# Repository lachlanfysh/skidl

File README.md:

# eda-mcp

Agent-callable PCB generation engine via MCP.

AI agents send a JSON circuit specification; the engine generates KiCad
schematics and PCB layouts. Structured exceptions with machine-readable
correction candidates let the agent fix and retry without natural language.

## Architecture

See [docs/ARCHITECTURE.md](docs/ARCHITECTURE.md) for the full pipeline,
module map, correction loop mechanics, and design decisions.

## Quick Start

Requirements: Python 3.10+, KiCad 9 (for symbol/footprint libraries),
system packages for pcbnew bindings.

```bash
# Install dependencies (editable install of the SKiDL engine)
pip install -e .

# Verify the schemas and translator
pytest tests/product/test_schemas.py -v

# Run the full product test suite
pytest tests/product/ -v

# Run the telemetry tests
pytest tests/product/test_telemetry.py -v

# Run the LLM operations tests (mocked, no API key needed)
pytest tests/product/test_llm.py -v
```

### Corpus Run

The corpus runner processes a manifest of boards through the pipeline with
checkpoint/resume and bounded concurrency.

```bash
# Engine-only mode (no LLM, uses cached specs)
python3 -m corpus.run_corpus --mode engine_only --no-mcp

# With LLM translation and review (needs OPENROUTER_API_KEY)
export OPENROUTER_API_KEY=sk-or-...
python3 -m corpus.run_corpus --mode internal --no-mcp --max-total-spend-usd 5

# Resume a stopped run (skips completed boards automatically)
python3 -m corpus.run_corpus --mode engine_only --no-mcp

# Force re-run of all boards
python3 -m corpus.run_corpus --mode engine_only --no-mcp --force
```

Results land in `telemetry/runs.jsonl` (one JSON record per board).

## Status

Overnight corpus run in progress. The morning data in
`telemetry/runs.jsonl` shows per-board pass/fail rates, correction loop
iterations, layout quality scores (HPWL, congestion), LLM token usage and
cost, and reference oracle similarity scores where available. This is the
primary feedback signal for engine improvements.

## Repo Layout

```
schemas/          JSON contract: CircuitSpec, DesignException, corrections
mcp_server/       MCP tool surface (generate_design, apply_correction)
llm/              OpenRouter client, design translation, exception review
telemetry/        RunRecord models, atomic JSONL store, geometry features
corpus/           Manifest runner, reference oracle, source fetcher
src/skidl/        SKiDL engine (dependency, not the product)
tests/product/    Product-layer test suite
```

## Not Open Source

This repo is private/proprietary. SKiDL (in `src/skidl/`) is MIT-licensed
upstream; everything else in this repo is not.

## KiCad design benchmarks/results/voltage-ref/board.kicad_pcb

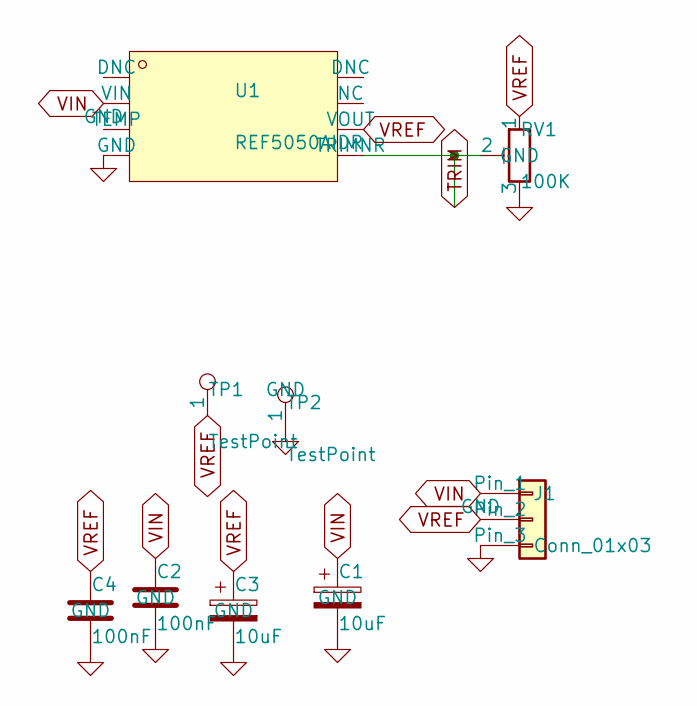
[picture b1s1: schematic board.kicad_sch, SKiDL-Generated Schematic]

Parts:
C1, C3: 10uF; CP_Elec_4x5.4
C2, C4: 100nF; C_0603_1608Metric
J1: Conn_01x03; PinHeader_1x03_P2.54mm_Vertical
RV1: 100K; Potentiometer_Bourns_3214W_Vertical
TP1, TP2: TestPoint; TestPoint_THTPad_1.5x1.5mm_Drill0.7mm
U1: REF5050AIDR; SOIC-8_3.9x4.9mm_P1.27mm

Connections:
GND: C1.2, C2.2, C3.2, C4.2, J1.3, RV1.3, TP2.1, U1.4 (GND)
TRIM: RV1.2, U1.5 (TRIMNR)
VIN: C1.1, C2.1, J1.1, U1.2 (VIN)
VREF: C3.1, C4.1, J1.2, RV1.1, TP1.1, U1.6 (VOUT)

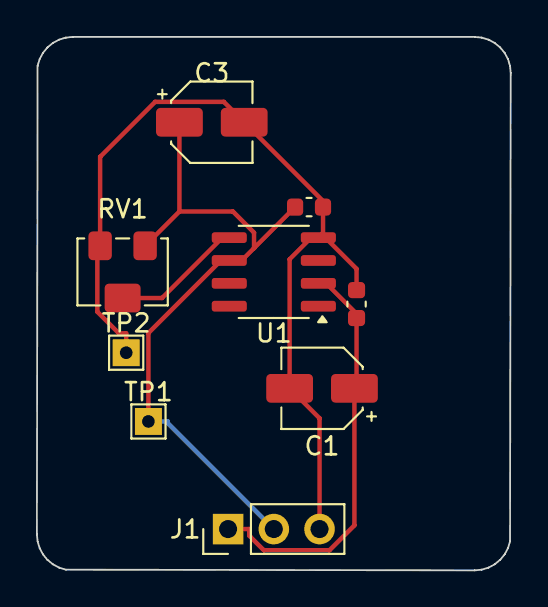
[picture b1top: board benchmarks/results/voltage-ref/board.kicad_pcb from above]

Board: 2 copper layers, 26.3 x 29.6 mm, 9 parts (0 on the bottom side), 4 nets.

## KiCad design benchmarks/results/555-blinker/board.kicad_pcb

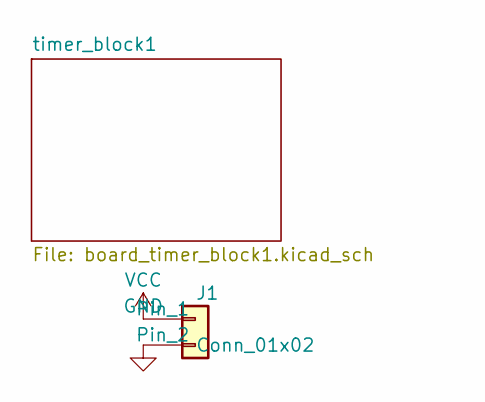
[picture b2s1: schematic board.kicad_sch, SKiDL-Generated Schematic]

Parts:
J1: Conn_01x02; PinHeader_1x02_P2.54mm_Vertical

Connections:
GND: J1.2; also elsewhere on the board
VCC: J1.1; also elsewhere on the board

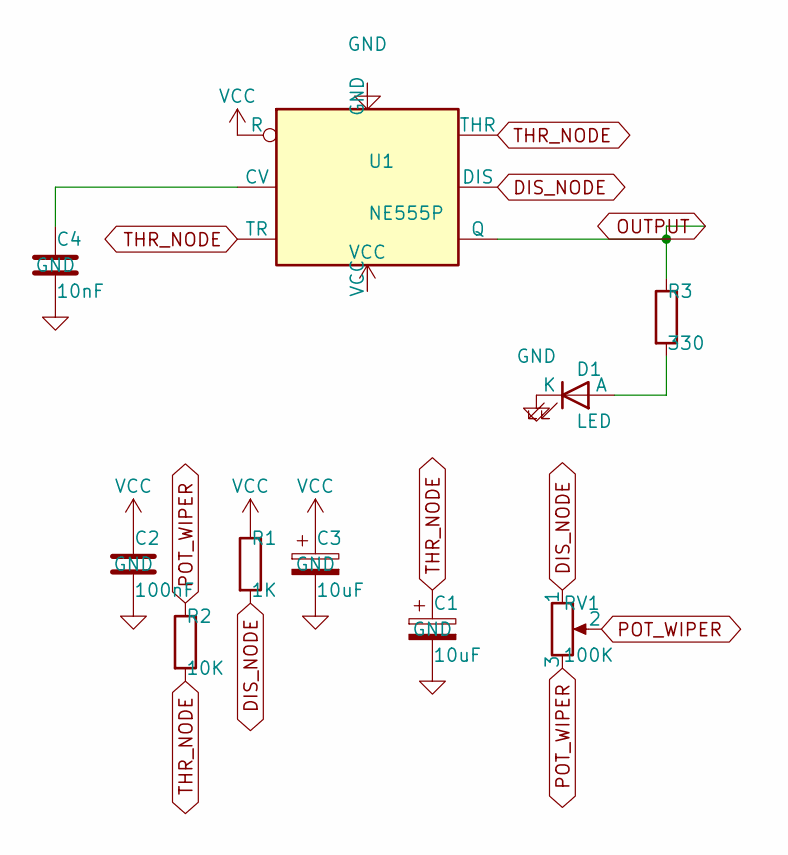
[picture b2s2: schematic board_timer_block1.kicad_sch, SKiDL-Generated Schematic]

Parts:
C1, C3: 10uF; CP_Radial_D6.3mm_P2.50mm
C2: 100nF; C_Disc_D3.0mm_W1.6mm_P2.50mm
C4: 10nF; C_Disc_D3.0mm_W1.6mm_P2.50mm
D1: LED; LED_D5.0mm
R1: 1K; R_Axial_DIN0207_L6.3mm_D2.5mm_P10.16mm_Horizontal
R2: 10K; R_Axial_DIN0207_L6.3mm_D2.5mm_P10.16mm_Horizontal
R3: 330; R_Axial_DIN0207_L6.3mm_D2.5mm_P10.16mm_Horizontal
RV1: 100K; Potentiometer_Bourns_3386P_Vertical
U1: NE555P; DIP-8_W7.62mm

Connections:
DIS_NODE: R1.2, RV1.1, U1.7 (DIS)
GND: C1.2, C2.2, C3.2, C4.2, D1.1 (K), U1.1 (GND); also elsewhere on the board
unnamed: C4.1, U1.5 (CV)
unnamed: D1.2 (A), R3.2
OUTPUT: R3.1, U1.3 (Q)
POT_WIPER: R2.1, RV1.2, RV1.3
THR_NODE: C1.1, R2.2, U1.2 (TR), U1.6 (THR)
VCC: C2.1, C3.1, R1.1, U1.4 (R), U1.8 (VCC); also elsewhere on the board

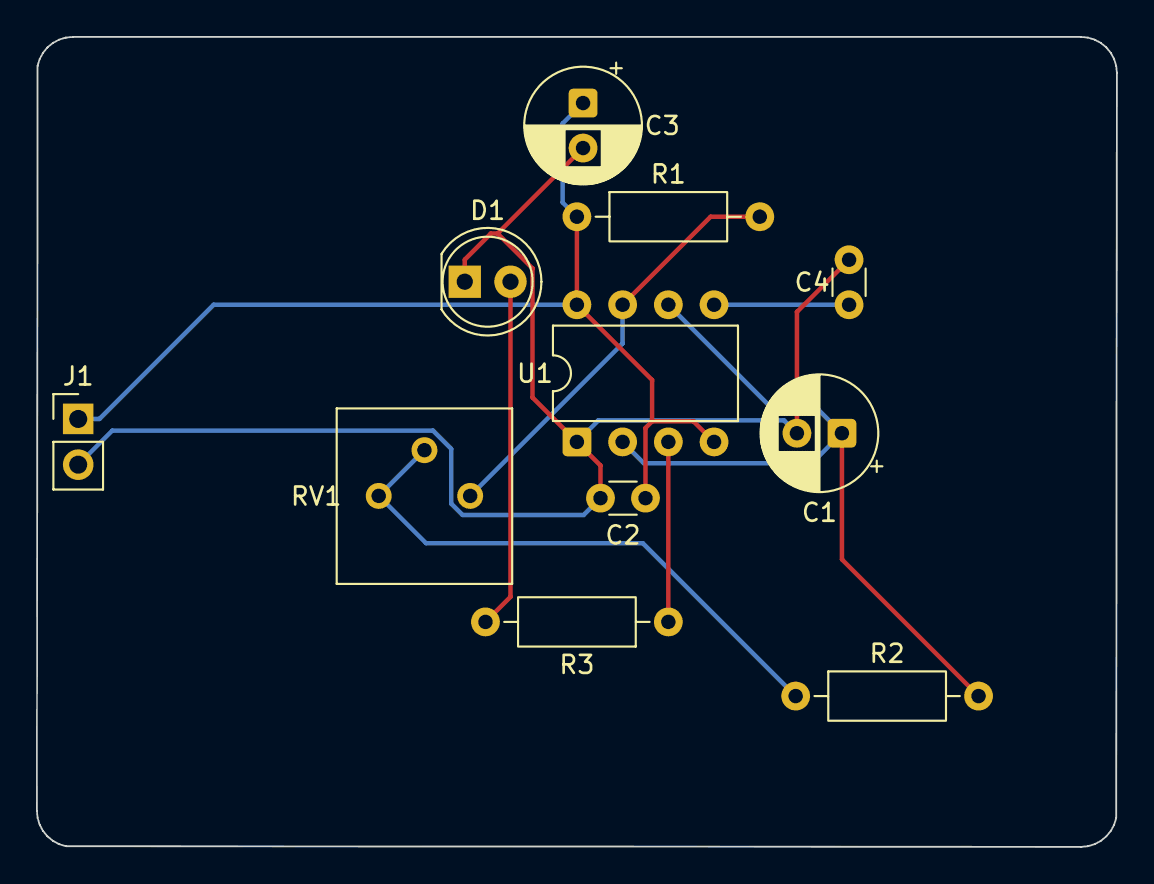
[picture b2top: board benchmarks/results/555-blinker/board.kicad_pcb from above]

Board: 2 copper layers, 60.0 x 45.0 mm, 11 parts (0 on the bottom side), 8 nets.

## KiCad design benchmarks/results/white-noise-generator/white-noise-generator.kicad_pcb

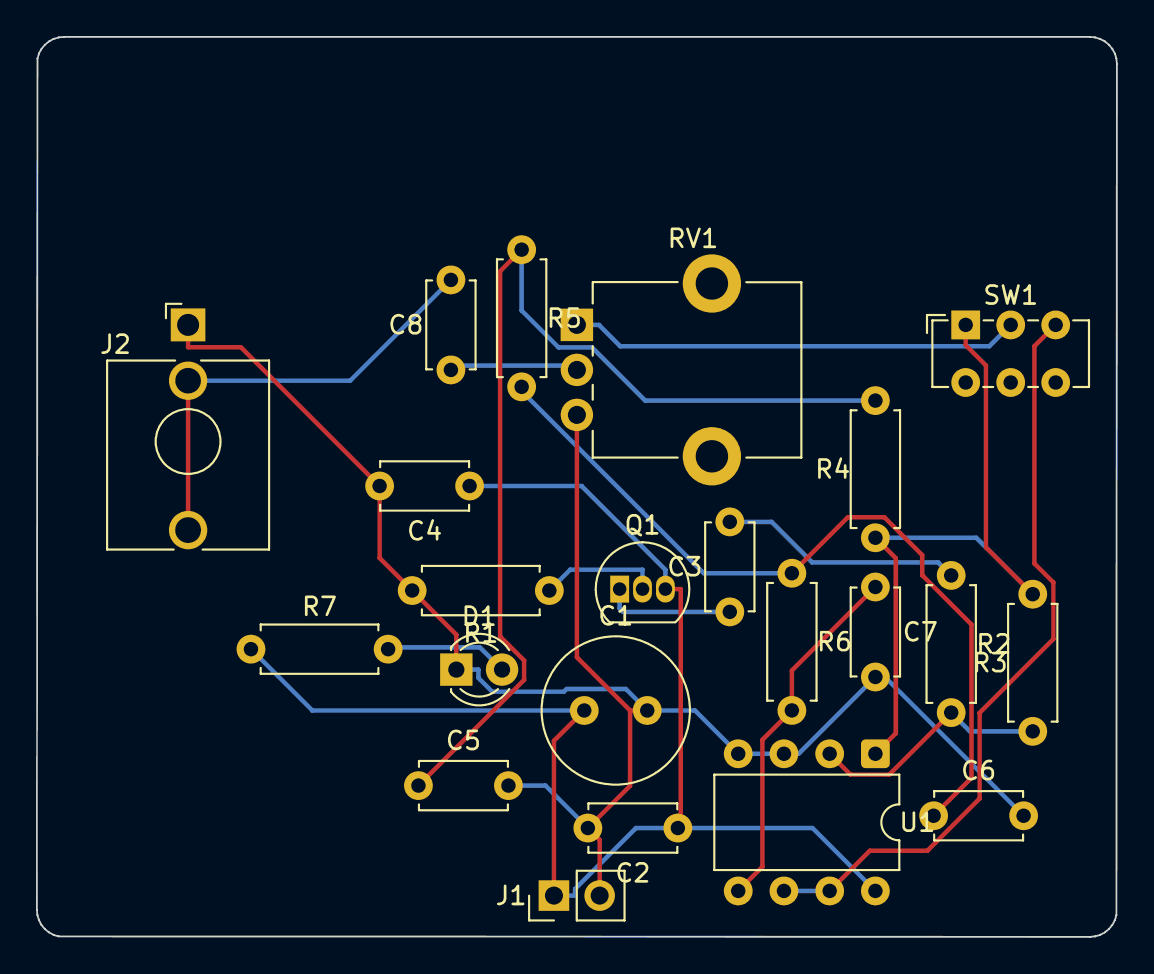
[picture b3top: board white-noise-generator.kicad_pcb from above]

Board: 2 copper layers, 60.0 x 50.0 mm, 22 parts (0 on the bottom side), 15 nets.

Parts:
C1: 100uF; C_Radial_D8.0mm_H11.5mm_P3.50mm
C2, C3, C4, C5, C8: 100nF; C_Disc_D4.7mm_W2.5mm_P5.00mm
C6: 10nF; C_Disc_D4.7mm_W2.5mm_P5.00mm
C7: 1nF; C_Disc_D4.7mm_W2.5mm_P5.00mm
D1: LED_GREEN; LED_D3.0mm
J1: 9V_IN; PinHeader_1x02_P2.54mm_Vertical
J2: OUT; Jack_3.5mm_QingPu_WQP-PJ398SM_Vertical_CircularHoles
Q1: BC547; TO-92_Inline
R1, R2, R5, R7: 10K; R_Axial_DIN0207_L6.3mm_D2.5mm_P7.62mm_Horizontal
R3: 1M; R_Axial_DIN0207_L6.3mm_D2.5mm_P7.62mm_Horizontal
R4: 100K; R_Axial_DIN0207_L6.3mm_D2.5mm_P7.62mm_Horizontal
R6: 1K; R_Axial_DIN0207_L6.3mm_D2.5mm_P7.62mm_Horizontal
RV1: B10K; Potentiometer_Alpha_RD901F-40-00D_Single_Vertical_CircularH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
SW1: WHITE/PINK; SW_E-Switch_EG1271_SPDT
U1: TL072; DIP-8_W7.62mm

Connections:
AMP_INV: R2.2, R3.1, U1.2
GND: C1.2, C2.2, C4.2, C5.2, C6.2, C7.2, D1.1, J1.2, J2.S, R1.2, RV1.3, U1.3, U1.4
LED_ANODE: D1.2, R7.2
unnamed: Q1.2, R1.1
NOISE_AMP_OUT: R3.2, R4.1, SW1.1, U1.1
NOISE_COUPLED: C3.2, R2.1
NOISE_RAW: C3.1, Q1.1
PINK_BUF_OUT: SW1.3, U1.6, U1.7
PINK_STAGE1: C5.1, R4.2, R5.1
PINK_STAGE2: C6.1, R5.2, R6.1
PINK_STAGE3: C7.1, R6.2, U1.5
SW_COMMON: RV1.1, SW1.2
VCC: C1.1, C2.1, C4.1, J1.1, Q1.3, R7.1, U1.8
VOL_IN: C8.2, J2.T, J2.TN
VOL_OUT: C8.1, RV1.2

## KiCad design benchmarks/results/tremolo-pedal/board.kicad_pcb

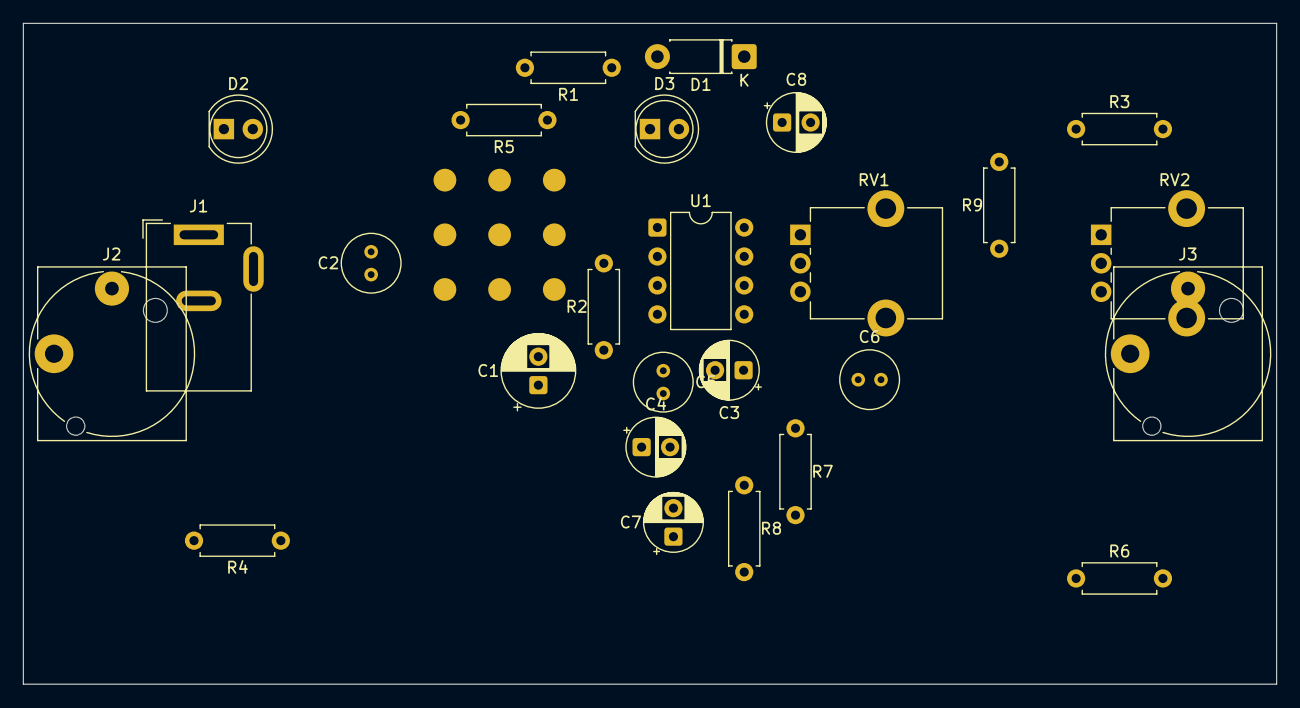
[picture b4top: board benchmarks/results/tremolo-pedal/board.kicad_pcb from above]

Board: 2 copper layers, 110.0 x 58.0 mm, 26 parts (0 on the bottom side), 13 nets, no tracks yet.

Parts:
C1: 100uF; CP_Radial_D6.3mm_P2.50mm
C2, C5, C6: 100nF; C_Radial_D5.0mm_H5.0mm_P2.00mm
C3, C4: 47uF; CP_Radial_D5.0mm_P2.50mm
C7, C8: 10uF; CP_Radial_D5.0mm_P2.50mm
D1: 1N4001; D_DO-41_SOD81_P7.62mm_Horizontal
D2: RED; LED_D5.0mm
D3: IR; LED_D5.0mm
J1: Barrel_Jack_Switch; BarrelJack_Wuerth_6941xx301002
J2, J3: AudioJack2; Jack_6.35mm_Neutrik_NJ2FD-V_Vertical
R1, R2, R4: 10K; R_Axial_DIN0207_L6.3mm_D2.5mm_P7.62mm_Horizontal
R3: 4.7K; R_Axial_DIN0207_L6.3mm_D2.5mm_P7.62mm_Horizontal
R5: 100K; R_Axial_DIN0207_L6.3mm_D2.5mm_P7.62mm_Horizontal
R6: 1K; R_Axial_DIN0207_L6.3mm_D2.5mm_P7.62mm_Horizontal
R7: 1M; R_Axial_DIN0207_L6.3mm_D2.5mm_P7.62mm_Horizontal
R8: LDR03; R_Axial_DIN0207_L6.3mm_D2.5mm_P7.62mm_Horizontal
R9: 100R; R_Axial_DIN0207_L6.3mm_D2.5mm_P7.62mm_Horizontal
RV1: 500K; Potentiometer_Alpha_RD901F-40-00D_Single_Vertical_CircularH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
RV2: 100K; Potentiometer_Alpha_RD901F-40-00D_Single_Vertical_CircularH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
U1: TL072; DIP-8_W7.62mm

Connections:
BYPASS_EFFECT: J3.T, R9.2
DEPTH_WIPER: C8.2, R9.1, RV2.2
GND: C1.2, C2.2, C3.2, C4.2, C5.2, D2.1, D3.1, J1.2, J1.3, J2.S, J3.S, R2.2, R8.2, RV1.3, RV2.3, U1.4
LED_DRIVE: D3.2, R6.2, RV2.1
LFO_OUT: C6.1, R5.1, R6.1, U1.1
LFO_RC: C6.2, R4.2, U1.2
unnamed: D2.2, R3.2
RATE_WIPER: R4.1, RV1.2
V9: C1.1, C2.1, D1.2, J1.1
VCA_BUF_OUT: C8.1, U1.6, U1.7
VCA_IN: C7.2, R7.1, R8.1, U1.5
VCC: C3.1, C5.1, D1.1, R1.1, RV1.1, U1.8
VREF: C4.1, R1.2, R2.1, R5.2, R7.2, U1.3

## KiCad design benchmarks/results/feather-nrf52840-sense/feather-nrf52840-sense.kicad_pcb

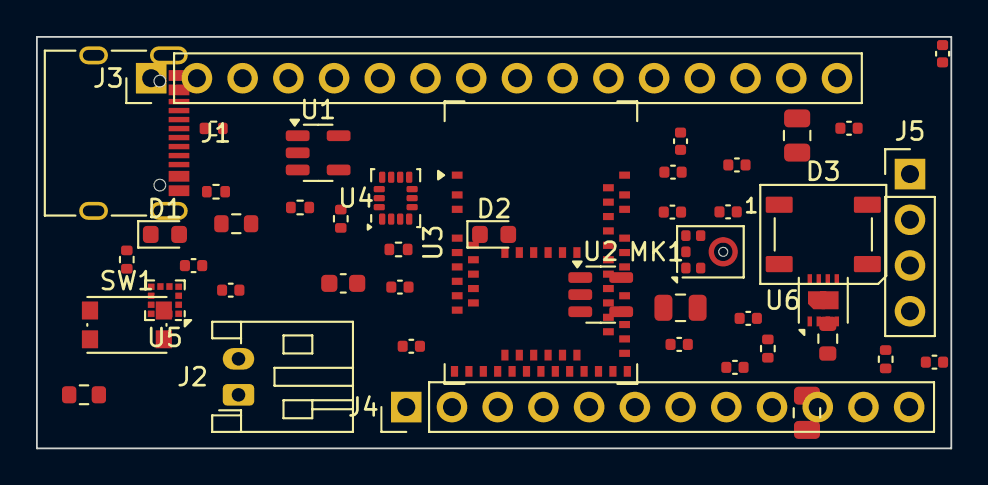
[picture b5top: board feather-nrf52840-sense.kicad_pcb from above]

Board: 2 copper layers, 50.8 x 22.9 mm, 46 parts (0 on the bottom side), 21 nets, no tracks yet.

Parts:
C1, C2, C4, C5, C7, C8, C9, C10, C12, C13, C14, C15, C16, C17, C18: 100nF; C_0402_1005Metric
C3, C6, C19: 10uF; C_0805_2012Metric
C11: 4.7uF; C_0603_1608Metric
D1: ORANGE; LED_0603_1608Metric
D2: RED; LED_0603_1608Metric
D3: WS2812B; LED_WS2812B_PLCC4_5.0x5.0mm_P3.2mm
J1: USB_C_Receptacle_USB2.0_16P; USB_C_Receptacle_XKB_U262-16XN-4BVC11
J2: Conn_01x02; JST_PH_S2B-PH-K_1x02_P2.00mm_Horizontal
J3: Conn_01x16; PinHeader_1x16_P2.54mm_Vertical
J4: Conn_01x12; PinHeader_1x12_P2.54mm_Vertical
J5: Conn_01x04; PinHeader_1x04_P2.54mm_Vertical
MK1: SPH0645LM4H; Knowles_SPH0645LM4H-6_3.5x2.65mm
R1, R2: 5.1K; R_0402_1005Metric
R3: 2K; R_0402_1005Metric
R4, R8: 1K; R_0402_1005Metric
R5, R6: 4.7K; R_0402_1005Metric
R7: 10K; R_0402_1005Metric
R9, R10, R11: 10K; R_0603_1608Metric
SW1: SW_Push; SW_Push_1P1T_NO_CK_KMR2
U1: MCP73831-2-OT; SOT-23-5
U2: AP2112K-3.3; SOT-23-5
U3: MDBT50Q-1MV2; Raytac_MDBT50Q
U4: LSM6DS33; LGA-14_3x2.5mm_P0.5mm_LayoutBorder3x4y
U5: LIS3MDL; LGA-12_2x2mm_P0.5mm
U6: SHT31-DIS; Sensirion_DFN-8-1EP_2.5x2.5mm_P0.5mm_EP1.1x1.7mm

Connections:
+3V3: C5.1, C6.1, C7.1, C8.1, C9.1, C10.1, C11.1, C13.1, C14.1, C16.1, C17.1, C18.1, D2.2, D3.1, J3.2, J5.1, MK1.5, R5.1, R6.1, R7.1, R9.1, R10.1, R11.1, U2.5, U3.28, U3.30, U4.5, U4.8, U4.12, U5.5, U5.6, U5.10, U6.5, U6.6
GND: C1.2, C2.2, C3.2, C4.2, C5.2, C6.2, C7.2, C8.2, C9.2, C10.2, C11.2, C12.2, C13.2, C14.2, C15.2, C16.2, C17.2, C18.2, C19.2, D3.3, J1.A1, J1.A12, J1.B1, J1.B12, J1.S1, J2.2, J3.4, J5.4, MK1.1, MK1.2, MK1.3, R1.2, R2.2, R3.2, SW1.2, U1.2, U2.2, U3.1, U3.2, U3.15, U3.33, U3.55, U4.1, U4.6, U4.7, U5.2, U5.3, U5.9, U5.12, U6.2, U6.8, U6.9
LED_RED_IO: R8.1, U3.8
MAG_DRDY: R10.2, U5.8
MAG_INT: R9.2, U5.7
unnamed: J1.A5, R1.1
unnamed: J1.B5, R2.1
unnamed: R3.1, U1.5
unnamed: R4.1, U1.1
unnamed: D1.1, R4.2
unnamed: D2.1, R8.2
unnamed: C12.1, U3.31
unnamed: C15.1, U5.4
SCL: J4.12, R6.2, U3.27, U4.13, U5.1, U6.4
SDA: J4.11, R5.2, U3.29, U4.14, U5.11, U6.1
SHT_ALERT: R11.2, U6.3
USB_DM: J1.A7, J1.B7, U3.34
USB_DP: J1.A6, J1.B6, U3.35
VBAT: C3.1, C4.1, J2.1, J4.1, U1.3, U2.1, U2.3
VBUS: C1.1, C2.1, C19.1, D1.2, J1.A4, J1.A9, J1.B4, J1.B9, J4.3, U1.4, U3.32
nRST: R7.2, SW1.1

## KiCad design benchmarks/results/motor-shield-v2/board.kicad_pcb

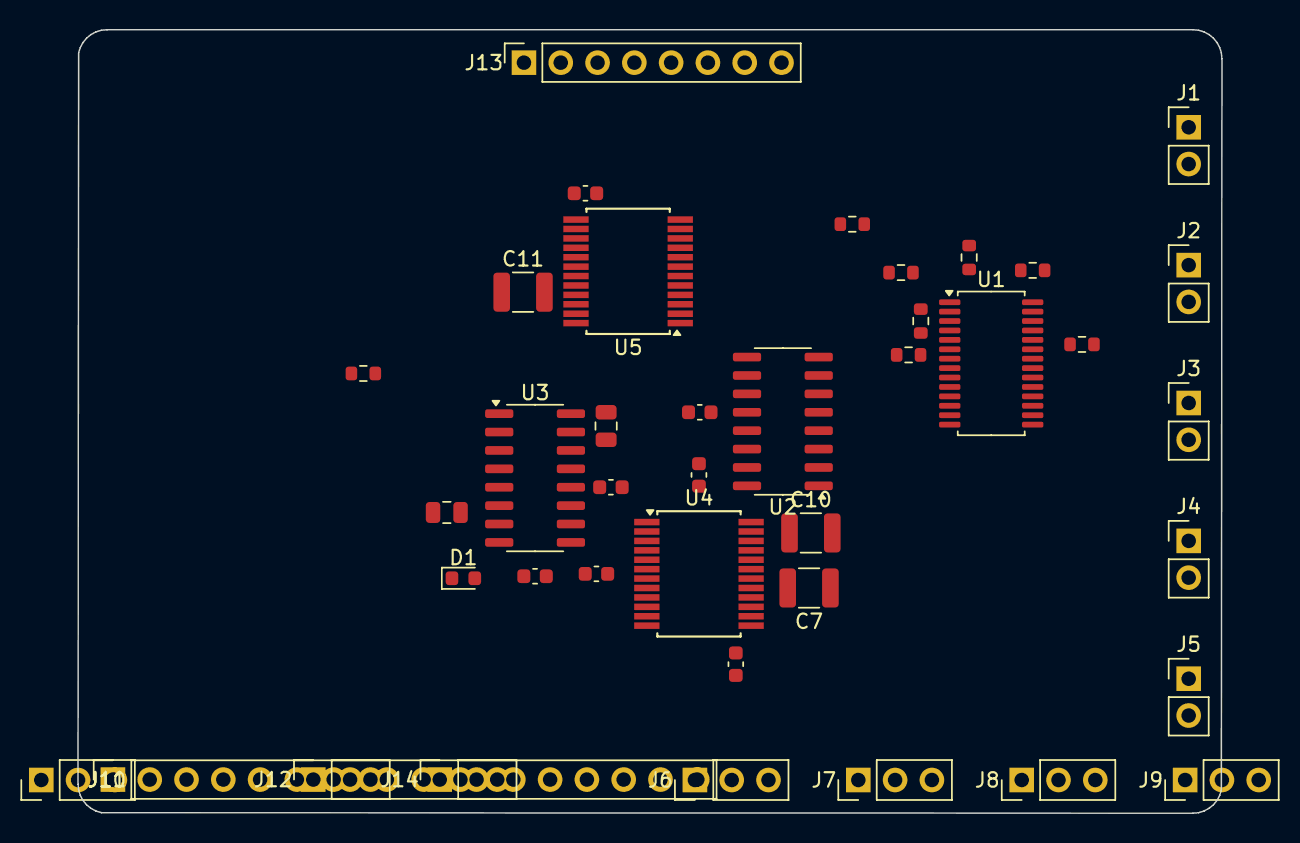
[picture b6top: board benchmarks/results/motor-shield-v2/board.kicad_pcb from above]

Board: 2 copper layers, 79.0 x 54.1 mm, 40 parts (0 on the bottom side), 38 nets, no tracks yet.

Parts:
C1, C3, C4, C5, C6, C8, C9: 100nF; C_0603_1608Metric
C2, C12: 10uF; C_0805_2012Metric
C7, C10: 47uF; C_1210_3225Metric
C11: 100uF; C_1210_3225Metric
D1: GREEN; LED_0603_1608Metric
J1: M1; PinHeader_1x02_P2.54mm_Vertical
J2: M2; PinHeader_1x02_P2.54mm_Vertical
J3: M3; PinHeader_1x02_P2.54mm_Vertical
J4: M4; PinHeader_1x02_P2.54mm_Vertical
J5: EXT_PWR; PinHeader_1x02_P2.54mm_Vertical
J6: A0_SEL; PinHeader_1x03_P2.54mm_Vertical
J7: A1_SEL; PinHeader_1x03_P2.54mm_Vertical
J8: A2_SEL; PinHeader_1x03_P2.54mm_Vertical
J9: A3_SEL; PinHeader_1x03_P2.54mm_Vertical
J10: A4_SEL; PinHeader_1x03_P2.54mm_Vertical
J11: PWR_HDR; PinSocket_1x08_P2.54mm_Vertical
J12: ADC_HDR; PinSocket_1x06_P2.54mm_Vertical
J13: DIG_HI_HDR; PinSocket_1x08_P2.54mm_Vertical
J14: DIG_LO_HDR; PinSocket_1x08_P2.54mm_Vertical
R1, R2: 4.7K; R_0603_1608Metric
R3, R4, R5, R6, R7: 10K; R_0603_1608Metric
R8: 1K; R_0603_1608Metric
U1: PCA9685PW; TSSOP-28_4.4x9.7mm_P0.65mm
U2, U3: 74HC595; SOIC-16_3.9x9.9mm_P1.27mm
U4, U5: TB6612FNG; SSOP-24_5.3x8.2mm_P0.65mm

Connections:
ADDR_A0: J6.2, R3.1, U1.1
ADDR_A1: J7.2, R4.1, U1.2
ADDR_A2: J8.2, R5.1, U1.3
ADDR_A3: J9.2, R6.1, U1.4
ADDR_A4: J10.2, R7.1, U1.5
GND: C1.2, C2.2, C3.2, C4.2, C5.2, C6.2, C7.2, C8.2, C9.2, C10.2, C11.2, C12.2, D1.2, J5.2, J6.1, J7.1, J8.1, J9.1, J10.1, J11.4, J11.5, J13.7, R3.2, R4.2, R5.2, R6.2, R7.2, U1.14, U1.23, U1.24, U1.25, U2.8, U2.13, U3.8, U3.13, U4.3, U4.4, U4.9, U4.10, U4.18, U5.3, U5.4, U5.9, U5.10, U5.18
M1A: J1.1, U4.1, U4.2
M1B: J1.2, U4.5, U4.6
M2A: J2.1, U4.11, U4.12
M2B: J2.2, U4.7, U4.8
M3A: J3.1, U5.1, U5.2
M3B: J3.2, U5.5, U5.6
M4A: J4.1, U5.11, U5.12
M4B: J4.2, U5.7, U5.8
unnamed: D1.1, R8.2
PWM0: U1.6, U4.23
PWM3: U1.9, U4.15
PWM8: U1.15, U5.23
PWM11: U1.18, U5.15
SCL: J12.6, R2.2, U1.26
SDA: J12.5, R1.2, U1.27
SR1_Q0: U2.15, U4.21
SR1_Q1: U2.1, U4.22
SR1_Q2: U2.2, U4.17
SR1_Q3: U2.3, U4.16
SR1_Q4: U2.4, U4.19
SR1_Q5: U2.5, U5.19
SR2_Q0: U3.15, U5.21
SR2_Q1: U3.1, U5.22
SR2_Q2: U3.2, U5.17
SR2_Q3: U3.3, U5.16
SR_CHAIN: U2.9, U3.14
SR_CLK: J13.6, U2.11, U3.11
SR_DATA: J13.4, U2.14
SR_LATCH: J14.7, U2.12, U3.12
VCC: C1.1, C2.1, C3.1, C4.1, C5.1, C8.1, J6.3, J7.3, J8.3, J9.3, J10.3, J11.3, R1.1, R2.1, R8.1, U1.28, U2.10, U2.16, U3.10, U3.16, U4.20, U5.20
VIN: C12.1, J11.6
VMOTOR: C6.1, C7.1, C9.1, C10.1, C11.1, J5.1, U4.13, U4.14, U4.24, U5.13, U5.14, U5.24

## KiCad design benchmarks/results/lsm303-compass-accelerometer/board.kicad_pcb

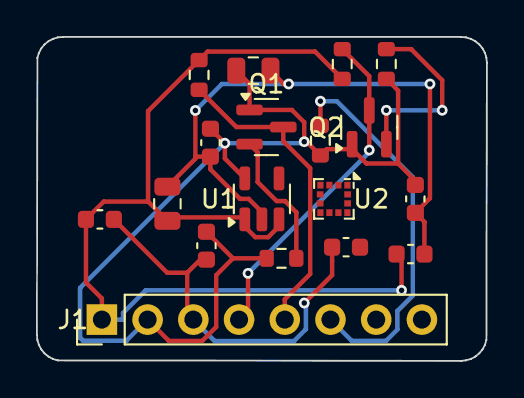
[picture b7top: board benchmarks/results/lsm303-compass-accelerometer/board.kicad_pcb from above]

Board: 2 copper layers, 25.0 x 18.0 mm, 18 parts (0 on the bottom side), 11 nets.

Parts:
C1, C5: 1uF; C_0603_1608Metric
C2, C3, C4, C6: 100nF; C_0603_1608Metric
C7, C8: 10uF; C_0805_2012Metric
J1: Conn_01x08; PinHeader_1x08_P2.54mm_Vertical
Q1, Q2: BSS138; SOT-23
R1, R2, R3, R4: 4.7K; R_0603_1608Metric
R5: 10K; R_0603_1608Metric
U1: AP2112K-3.3; SOT-23-5
U2: LSM303AGRTR; LGA-12_2x2mm_P0.5mm

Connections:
3V3: C2.1, C4.1, C5.1, C7.1, J1.2, Q1.1, Q2.1, R1.1, R3.1, R5.1, U1.5, U2.2, U2.3, U2.9, U2.10
C1_BYPASS: C3.1, U2.5
DRDY: J1.6, R5.2, U2.7
GND: C1.2, C2.2, C3.2, C4.2, C5.2, C6.2, C7.2, C8.2, J1.3, U1.2, U2.6, U2.8
INT1: J1.7, U2.12
INT2: J1.8, U2.11
SCL: J1.4, Q2.3, R4.2
SCL_33: Q2.2, R3.2, U2.1
SDA: J1.5, Q1.3, R2.2
SDA_33: Q1.2, R1.2, U2.4
VIN: C1.1, C6.1, C8.1, J1.1, R2.1, R4.1, U1.1, U1.3

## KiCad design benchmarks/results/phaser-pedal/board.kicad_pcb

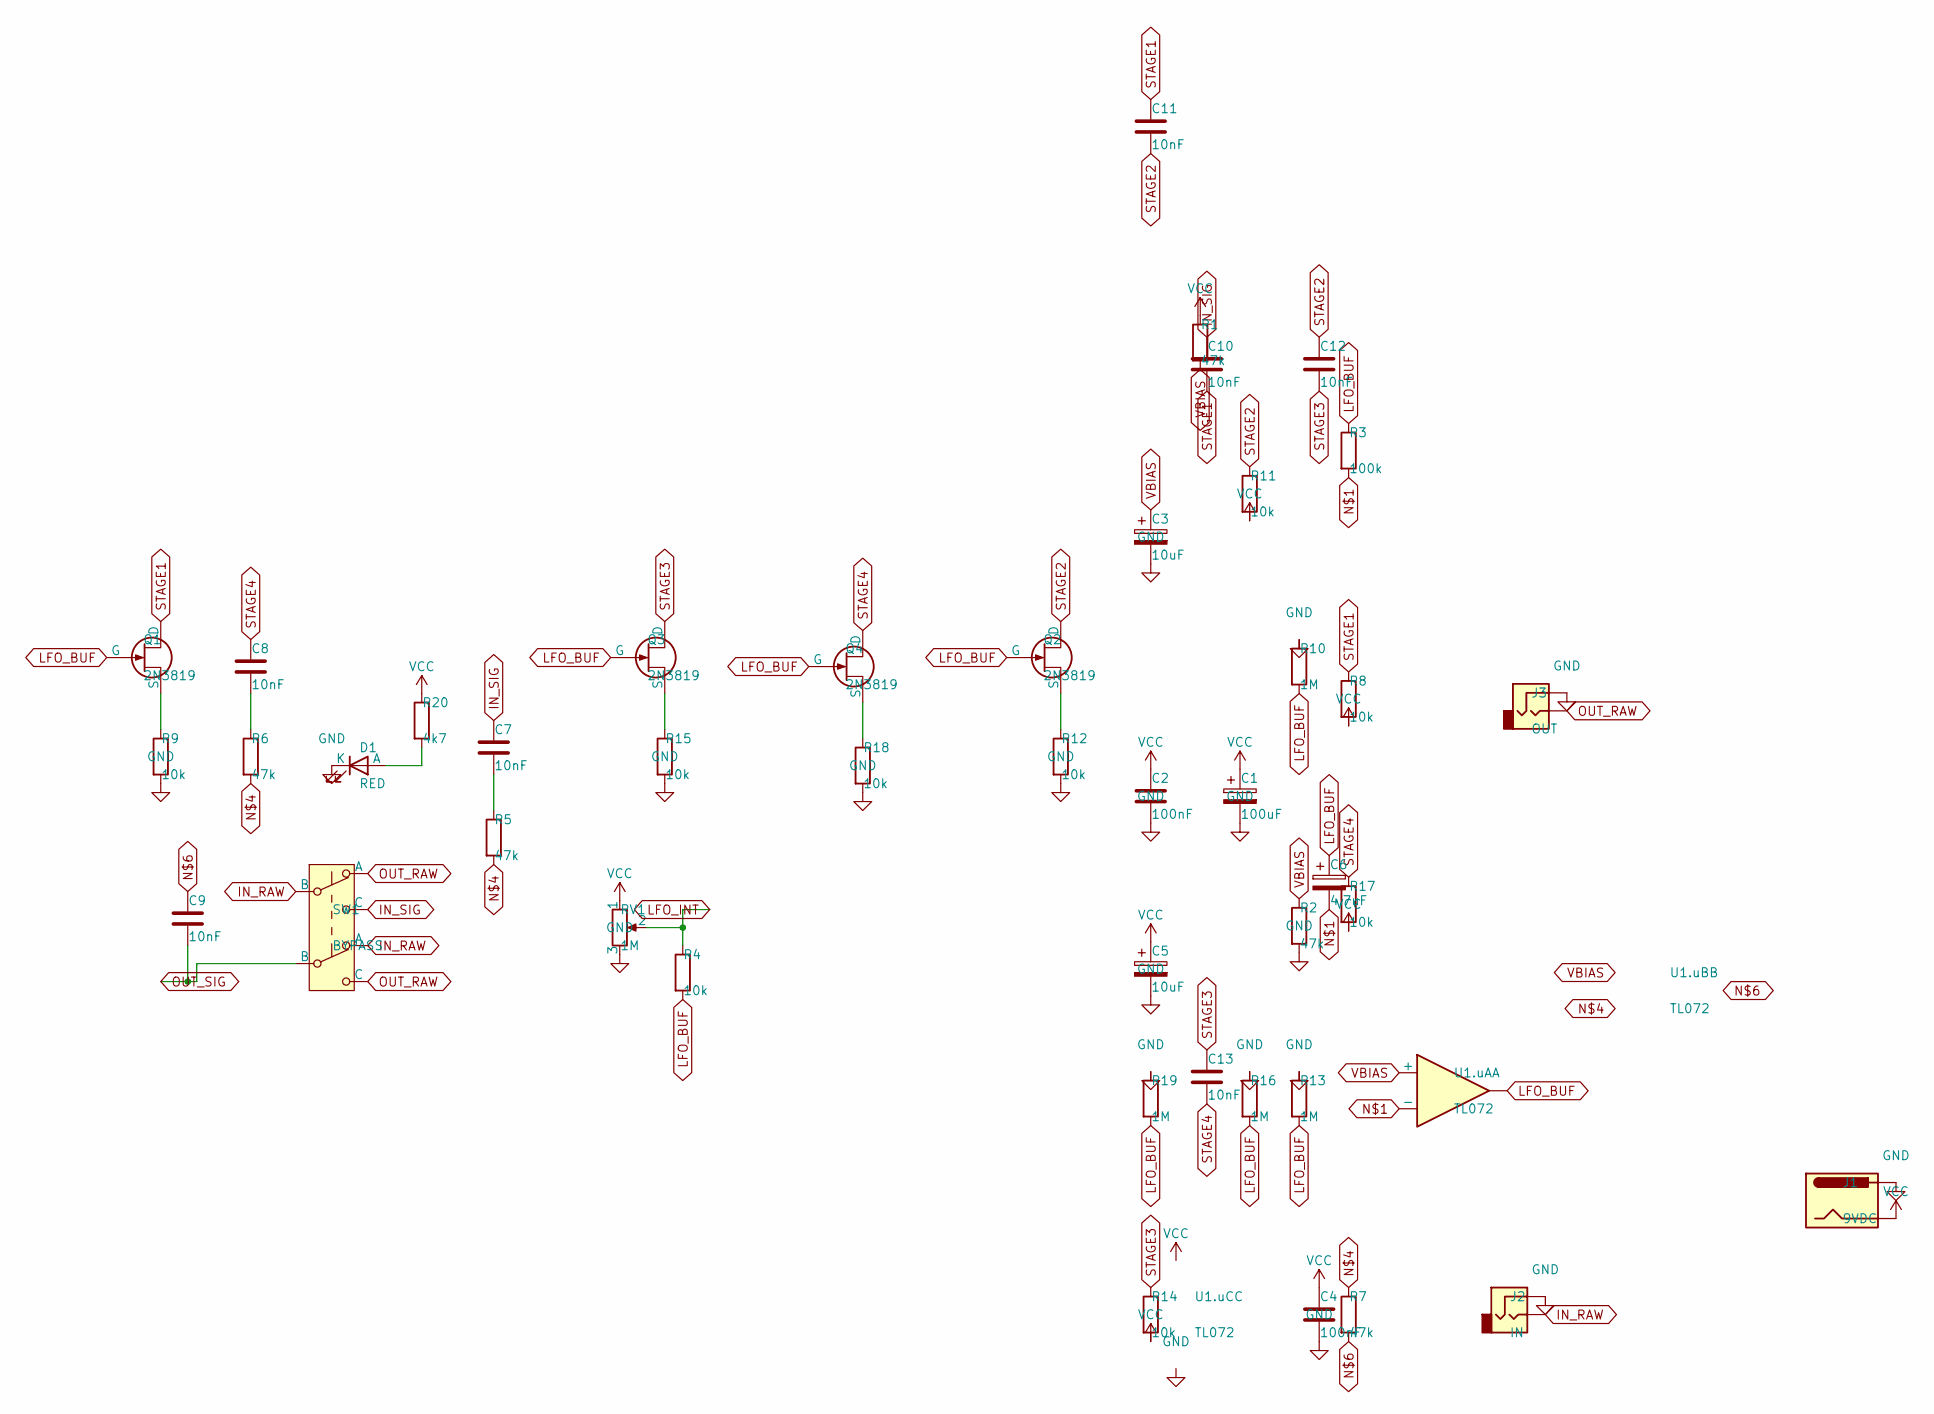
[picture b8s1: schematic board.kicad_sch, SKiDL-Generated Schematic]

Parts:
C1: 100uF; CP_Radial_D8.0mm_P3.50mm
C2, C4: 100nF; C_Disc_D5.0mm_W2.5mm_P5.00mm
C3, C5: 10uF; CP_Radial_D5.0mm_P2.50mm
C6: 4.7uF; CP_Radial_D5.0mm_P2.50mm
C7, C8, C9, C10, C11, C12, C13: 10nF; C_Disc_D5.0mm_W2.5mm_P5.00mm
D1: RED; LED_D3.0mm
J1: 9VDC; BarrelJack_CUI_PJ-063AH_Horizontal
J2: IN; Jack_6.35mm_Neutrik_NJ2FD-V_Vertical
J3: OUT; Jack_6.35mm_Neutrik_NJ2FD-V_Vertical
Q1, Q2, Q3, Q4: 2N3819; TO-92
R1, R2, R5, R6, R7: 47k; R_Axial_DIN0207_L6.3mm_D2.5mm_P10.16mm_Horizontal
R3: 100k; R_Axial_DIN0207_L6.3mm_D2.5mm_P10.16mm_Horizontal
R4, R8, R9, R11, R12, R14, R15, R17, R18: 10k; R_Axial_DIN0207_L6.3mm_D2.5mm_P10.16mm_Horizontal
R10, R13, R16, R19: 1M; R_Axial_DIN0207_L6.3mm_D2.5mm_P10.16mm_Horizontal
R20: 4k7; R_Axial_DIN0207_L6.3mm_D2.5mm_P10.16mm_Horizontal
RV1: 1M; Potentiometer_Alpha_RD901F-40-00D_Single_Vertical
SW1: BYPASS; SW_PUSH_E-Switch_FS5700DP_DPDT
U1.uA, U1.uB, U1.uC: TL072

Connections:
GND: C1.2, C2.2, C3.2, C4.2, C5.2, D1.1 (K), J1.1, J2.S, J3.S, R2.2, R9.2, R10.1, R12.2, R13.1, R15.2, R16.1, R18.2, R19.1, RV1.3; also elsewhere on the board
IN_RAW: J2.T, SW1.2 (B), SW1.4 (A)
IN_SIG: C7.1, C10.1, SW1.3 (C)
LFO_BUF: C6.1, Q1.2 (G), Q2.2 (G), Q3.2 (G), Q4.2 (G), R3.1, R4.2, R10.2, R13.2, R16.2, R19.2, U1.uA.1; also elsewhere on the board
LFO_INT: R4.1, RV1.2
unnamed 5: C6.2, R3.2, U1.uA.2 (-); also elsewhere on the board
unnamed: C7.2, R5.1
unnamed 7: R5.2, R6.2, R7.1; also elsewhere on the board
unnamed: C8.2, R6.1
unnamed 9: C9.1, R7.2; also elsewhere on the board
unnamed: Q1.3 (S), R9.1
unnamed: Q2.3 (S), R12.1
unnamed: Q3.3 (S), R15.1
unnamed: Q4.3 (S), R18.1
unnamed: D1.2 (A), R20.2
OUT_RAW: J3.T, SW1.1 (A), SW1.6 (C)
OUT_SIG: C9.2, SW1.5 (B)
STAGE1: C10.2, C11.1, Q1.1 (D), R8.1
STAGE2: C11.2, C12.1, Q2.1 (D), R11.1
STAGE3: C12.2, C13.1, Q3.1 (D), R14.1
STAGE4: C8.1, C13.2, Q4.1 (D), R17.1
VBIAS: C3.1, R1.2, R2.1, U1.uA.3 (+); also elsewhere on the board
VCC: C1.1, C2.1, C4.1, C5.1, J1.2, R1.1, R8.2, R11.2, R14.2, R17.2, R20.1, RV1.1; also elsewhere on the board

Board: 2 copper layers, 44 parts (0 on the bottom side), 23 nets, no tracks yet.

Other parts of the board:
U1: TL072; DIP-8_W7.62mm

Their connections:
GND: U1.4; also elsewhere on the board
LFO_BUF: U1.1; also elsewhere on the board
unnamed 5: U1.2; also elsewhere on the board
unnamed 7: U1.6; also elsewhere on the board
unnamed 9: U1.7; also elsewhere on the board
VBIAS: U1.3, U1.5; also elsewhere on the board
VCC: U1.8; also elsewhere on the board

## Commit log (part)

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2026-06-02 notes: fix EN-fix commit hash in #302 draft (846d8999)
2026-06-02 notes: #302 draft — drop MR1, embed real render images (raw URLs)
2026-06-02 notes: #302 draft — esp32 as orientation proof, transistor before/after for grid_blocks
2026-06-02 notes: esp32 render — wider crop incl. decoupling-cap fan, EN net named (no N$9)
2026-06-02 notes: #302 draft — clean on-pin transistor render + deconflict fix in table; drop grid before/after
2026-06-02 notes: #302 reply to Dave (net-label question)
2026-06-03 feat(netlist): mirror durable Group field into kicad6/7/8 generators
2026-06-06 Add layout planning and KiCad smoke validation
2026-06-06 Add region and edge-aware layout placement
2026-06-06 Add intent-aware placement candidates
2026-06-06 Improve placement orientation and power corridors
2026-06-06 Document elite placer handoff plan
2026-06-06 Add mechanical mating intent inference
2026-06-06 Fix layout footprint alias compatibility
2026-06-06 Add actual-pin decap placement refinement
2026-06-06 Add power topology placement candidate
2026-06-06 Add repeated-channel slot model
2026-06-06 Add congestion heatmap scoring
2026-06-06 Add local placement refinement
2026-06-06 Add placement report explainability helpers
2026-06-06 Add net attribution to placement reports
2026-06-06 Add report invariants to layout benchmark corpus
2026-06-07 docs: add agent simulation and layout workflow guidance
2026-06-10 phase2: add MCP server pipeline
2026-06-10 phase3b: add corpus runner
2026-06-10 phase3b: add generate policy and runner hardening
2026-06-13 docs: add Codex agent guidance
2026-06-13 fix: align MCP surface with SKiDL workflow
2026-06-13 fix: run design review for SKiDL code jobs
2026-06-13 chore: document Railway autodeploy path
2026-06-13 chore: make Railway deploy workflow inert until configured
2026-06-13 fix: make MCP failures actionable
2026-06-13 fix: hide legacy json mcp workflow
2026-06-13 fix: enforce manufacturable output gate
2026-06-13 fix: report missing pcb footprints
2026-06-13 test: harden agent probe guidance
2026-06-13 fix: classify schematic routing crashes
2026-06-13 fix: spread edge connectors and improve footprint search
2026-06-13 fix: keep refined decaps out of parent footprints
2026-06-13 fix: classify post-artifact worker failures
2026-06-13 test: harvest active jobs at probe turn cap
2026-06-13 fix: clarify SKiDL net expression errors
2026-06-13 fix: legalize placement overlaps during refinement
2026-06-13 test: accept markdown final report markers
2026-06-13 docs: clarify mounting holes and test points
2026-06-13 fix: harden schematic placement and overlap legalization
2026-06-13 test: tolerate malformed OpenRouter responses
2026-06-13 fix: make manufacturing status explicit on failures
2026-06-13 fix: pass router timeout through MCP pipeline
2026-06-13 fix: surface actionable exceptions first
2026-06-13 fix: recover stale railway jobs
2026-06-13 fix: compact get_job results for agents
2026-06-13 fix: omit job specs from polling responses
2026-06-13 fix: trim job summaries for polling agents
2026-06-13 fix: reconnect MCP probe sessions after deploys
2026-06-13 fix: reap stale running jobs periodically
2026-06-13 fix: isolate native routing and expand overlap legalization
2026-06-13 fix: restore converted lcsc assets for workers
2026-06-13 fix: improve code diagnostics and control roles
2026-06-13 fix: improve connector and routing feedback
2026-06-13 fix: parse numeric pin diagnostics
2026-06-13 fix: sharpen agent feedback loops
2026-06-13 fix: return pin details for multiple symbol matches
2026-06-13 fix: improve connector search feedback
2026-06-13 fix: distinguish din midi connector search
2026-06-13 fix: watch llm files for railway deploys
2026-06-13 fix: improve switch and part repair hints
2026-06-13 fix: prefer generic switch symbols
2026-06-13 fix: expose converted part pin details
2026-06-13 fix: preserve pin family hints from stderr
2026-06-13 fix: guide agents through keypad and module choices
2026-06-13 fix: sharpen layout and pin retry guidance
2026-06-13 fix: harden routing export and probe timeouts
2026-06-13 fix: improve component search retry guidance
2026-06-13 fix: add common component retry hints
2026-06-14 feat: add beta signup access flow
2026-06-14 style: refine beta signup page
2026-06-14 feat: refine beta signup and layout feedback loop
2026-06-14 Improve layout recovery and module socket intent
2026-06-14 Recover Specctra routing from KiCad metadata crashes
2026-06-14 Distinguish edge audio jacks from panel jacks
2026-06-14 Keep edge connectors out of repeated-channel grids
2026-06-14 Improve corpus-backed layout templates
2026-06-15 Improve layout assembly side policy
2026-06-15 Expose explicit edge placement hints
2026-06-15 Expose explicit edge rotation hints
2026-06-15 Improve edge connector placement heuristics
2026-06-15 Improve breakout connector and preview artifact handling
2026-06-15 Add placement review goal for hosted MCP
2026-06-15 Keep passives clear of mounting holes
2026-06-15 Allow inline custom footprints in code submissions
2026-06-15 Improve mechanical placement feedback
2026-06-15 Avoid duplicate Qwiic enrichment
2026-06-15 Tell agents to preserve best placement candidate
2026-06-15 Keep edge anchors clear of mounting holes
2026-06-15 Guide agents away from fixed edge connectors
2026-06-15 Avoid pin xy fallback crash in auto-stub
2026-06-15 Clarify overlap feedback for fixed floorplans
2026-06-15 Fallback to mockup preview when KiCad export fails
2026-06-15 Skip stub labels for unconnected pins
2026-06-15 Tolerate pin-like objects in schematic net walks
2026-06-15 Harden schematic generation for pin-like objects
2026-06-15 Expose custom footprints in SKiDL submissions
2026-06-15 Ignore signal nets in power-rail review
2026-06-15 Require supply evidence for power rail enrichment
2026-06-15 Require IC pin evidence for local supply rails
2026-06-15 Clarify multi-unit pin errors
2026-06-15 Surface power analysis metrics
2026-06-15 Tighten MCP polling and floorplan guidance
2026-06-15 Improve MCP feedback and power analysis
2026-06-15 Improve direct MCP testing feedback
2026-06-16 Improve product layout engine feedback
2026-06-16 Add layout quality reporting
2026-06-16 Improve product layout validation
2026-06-16 Improve Wave 1 layout heuristics
2026-06-16 Track Wave 2 layout agents
2026-06-16 Integrate Wave 2 MCP layout contracts
2026-06-16 Record Wave 2 hosted smoke results
2026-06-16 Report lost workers as structured engine crashes
2026-06-16 Classify same-footprint DRC failures as footprint issues
2026-06-16 Record hosted routing diagnosis verification
2026-06-16 Add owner worker-loss sentinel probe
2026-06-16 Record worker-loss sentinel verification
2026-06-16 Mark layout uplift lanes hosted verified
2026-06-16 Improve layout quality and MCP review feedback
2026-06-16 Improve hosted layout validation and edge anchoring
2026-06-17 Improve hosted layout recovery and floorplan handling
2026-06-17 Improve placement review and connector layout feedback
2026-06-17 Stabilize hosted layout placement feedback
2026-06-17 Treat reviewable failures as terminal
2026-06-17 Tighten hosted placement recovery
2026-06-17 Add hosted job progress heartbeats
2026-06-17 Preflight contradictory floorplans
2026-06-17 Improve floorplan guidance and bus passive placement
2026-06-17 Fix module socket intent and floorplan overlap feedback
2026-06-17 Avoid RF intent on generic module sockets
